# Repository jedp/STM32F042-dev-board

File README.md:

## STM32F042 Board

Dev board for the
[STM32F042](https://www.st.com/resource/en/datasheet/stm32f042c4.pdf).

Basic linker script, headers, hello world program, and notes are given in [programming](./programming).

Dimensions: 1.63in (41.50mm) x 0.74 in (18.80mm); headers 0.6in (15.24mm) center to center.

USB C receptacle for USB 2.0.

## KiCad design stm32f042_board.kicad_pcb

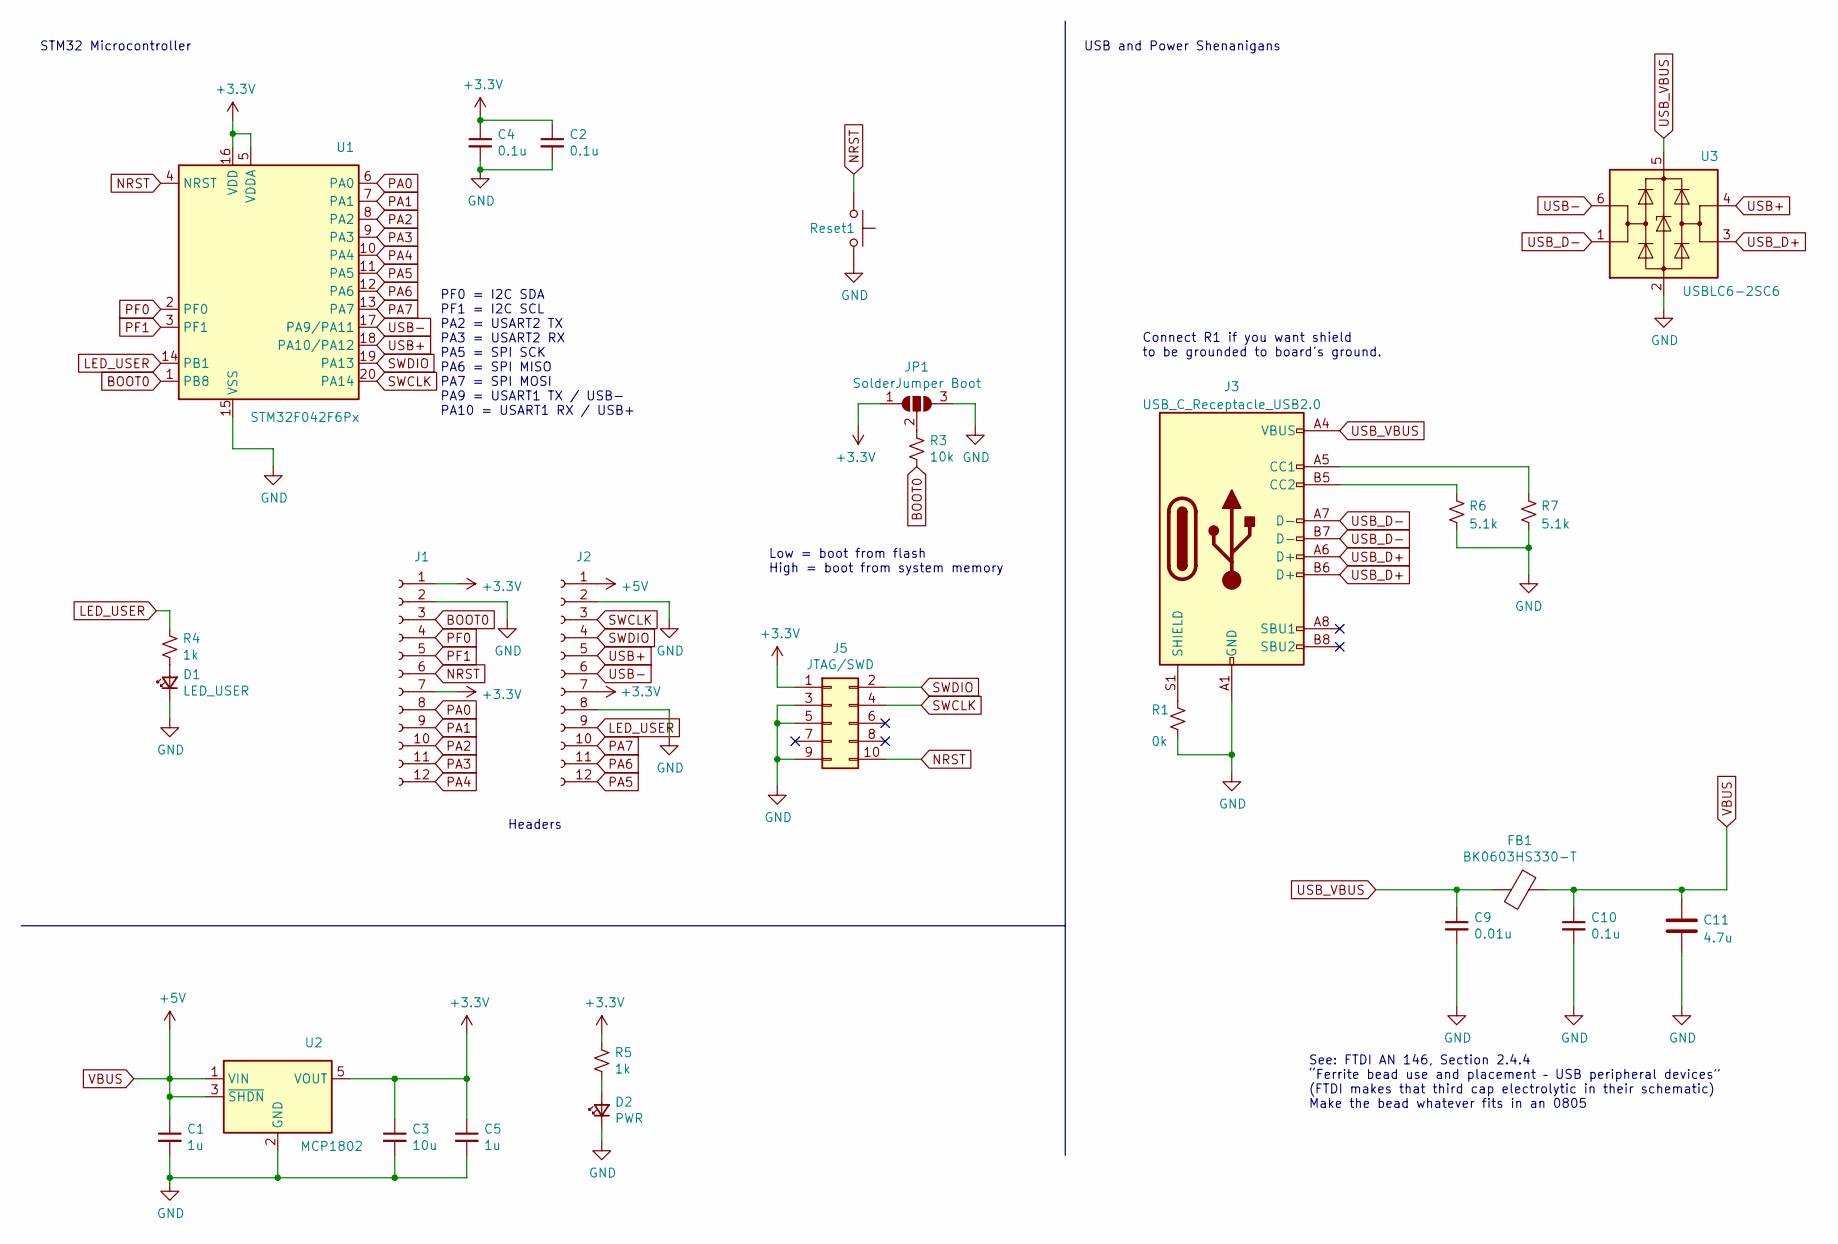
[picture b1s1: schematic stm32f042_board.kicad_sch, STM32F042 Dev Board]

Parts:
C1, C5: 1u; C_0805_2012Metric
C2, C4: 0.1u; C_0603_1608Metric
C3: 10u; C_0805_2012Metric
C9: 0.01u; C_0805_2012Metric
C10: 0.1u; C_0805_2012Metric
C11: 4.7u; C_1206_3216Metric
D1: LED_USER; LED_0603_1608Metric
D2: PWR; LED_0603_1608Metric
FB1: BK0603HS330-T; L_0805_2012Metric
J1, J2: Conn_01x12_Female; PinSocket_1x12_P2.54mm_Vertical
J3: USB_C_Receptacle_USB2.0; USB4105-GF-A
J5: JTAG/SWD; PinHeader_2x05_P1.27mm_Vertical
JP1: SolderJumper Boot; SolderJumper-3_P2.0mm_Open_TrianglePad1.0x1.5mm
R1: 0k; R_0603_1608Metric
R3: 10k; R_0603_1608Metric
R4, R5: 1k; R_0603_1608Metric
R6, R7: 5.1k; R_0603_1608Metric
Reset1: SW_Push; SW_SPST_B3U-1000P-B
U1: STM32F042F6Px; TSSOP-20_4.4x6.5mm_P0.65mm
U2: MCP1802; SOT-23-5
U3: USBLC6-2SC6; SOT-23-6

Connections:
+3V3: C2.1, C3.1, C4.1, C5.1, J1.1, J1.7, J2.7, J5.1, JP1.1 (A), R5.1, U1.5 (VDDA), U1.16 (VDD), U2.5 (VOUT)
BOOT0: J1.3, R3.2, U1.1 (PB8)
GND: C1.2, C2.2, C3.2, C4.2, C5.2, C9.2, C10.2, C11.2, D1.1 (K), D2.1 (K), J1.2, J2.2, J2.8, J3.A1 (GND), J3.A12 (GND), J3.B1 (GND), J3.B12 (GND), J5.3, J5.5, J5.9, JP1.3 (B), R1.2, R6.2, R7.2, Reset1.2, U1.15 (VSS), U2.2 (GND), U3.2 (GND)
LED_USER: J2.9, R4.1, U1.14 (PB1)
NRST: J1.6, J5.10, Reset1.1, U1.4 (NRST)
unnamed: D1.2 (A), R4.2
unnamed: D2.2 (A), R5.2
unnamed: J3.A5 (CC1), R7.1
unnamed: J3.B5 (CC2), R6.1
unnamed: J3.S1 (SHIELD), R1.1
unnamed: JP1.2 (C), R3.1
PA0: J1.8, U1.6 (PA0)
PA1: J1.9, U1.7 (PA1)
PA2: J1.10, U1.8 (PA2)
PA3: J1.11, U1.9 (PA3)
PA4: J1.12, U1.10 (PA4)
PA5: J2.12, U1.11 (PA5)
PA6: J2.11, U1.12 (PA6)
PA7: J2.10, U1.13 (PA7)
PF0: J1.4, U1.2 (PF0)
PF1: J1.5, U1.3 (PF1)
SWCLK: J2.3, J5.4, U1.20 (PA14)
SWDIO: J2.4, J5.2, U1.19 (PA13)
USB+: J2.5, U1.18 (PA10/PA12), U3.4 (I/O2)
USB-: J2.6, U1.17 (PA9/PA11), U3.6 (I/O1)
USB_D+: J3.A6 (D+), J3.B6 (D+), U3.3 (I/O2)
USB_D-: J3.A7 (D-), J3.B7 (D-), U3.1 (I/O1)
USB_VBUS: C9.1, FB1.2, J3.A4 (VBUS), J3.A9 (VBUS), J3.B4 (VBUS), J3.B9 (VBUS), U3.5 (VBUS)
VBUS: C1.1, C10.1, C11.1, FB1.1, J2.1, U2.1 (VIN), U2.3 (~SHDN)

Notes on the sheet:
Headers
Connect R1 if you want shield to be grounded to board's ground.
PF0 = I2C SDA PF1 = I2C SCL PA2 = USART2 TX PA3 = USART2 RX PA5 = SPI SCK PA6 = SPI MISO PA7 = SPI MOSI PA9 = USART1 TX / USB- PA10 = USART1 RX / USB+
STM32 Microcontroller
USB and Power Shenanigans
See: FTDI AN 146, Section 2.4.4 “Ferrite bead use and placement – USB peripheral devices” (FTDI makes that third cap electrolytic in their schematic) Make the bead whatever fits in an 0805
Low = boot from flash High = boot from system memory

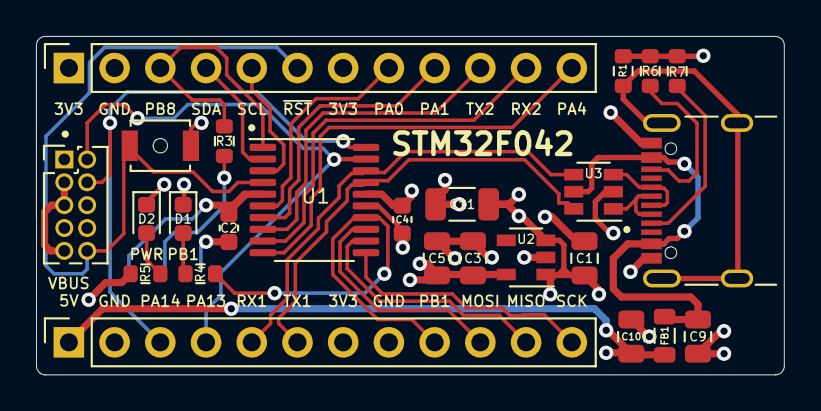
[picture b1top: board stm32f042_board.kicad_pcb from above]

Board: 4 copper layers, 41.6 x 18.8 mm, 26 parts (1 on the bottom side), 29 nets.

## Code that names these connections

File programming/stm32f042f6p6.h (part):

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 *
 * TSSOP20 Pinout, with alternate and additional functions.
 *
 *   1 PB8, BOOT0
 *   2 PF0, OSC_IN, CRS_SYNC, I2C1_SDA
 *   3 PF1, OSC_OUT, I2C1_SCL
 *   4 NRST
 *   5 VDDA
 *   6 PA0, USART2_CTS, TIM2_CH1_ETR, TSC_G1_IO1, RTC_TAMP2, WKUP1, ADC_IN0
 *   7 PA1, USART2_RTS, TIM2_CH2, TSC_G1_IO2, EVENTOUT, ADC_IN1
 *   8 PA2, USART2_TX, TIM2_CH3, TSC_G1_IO3, ADC_IN2, WKUP4
 *   9 PA3, USART2_RX, TIM2_CH4, TSC_G1_IO4, ADC_IN3
 *  10 PA4, SPI1_NSS, I2S1_WS, TIM14_CH1, TSC_G2_IO1, USART2_CK USB_NOE, ADC_IN4
 *  11 PA5, SPI1_SCK, I2S1_CK, CEC, TIM2_CH1_ETR, TSC_G2_IO2, ADC_IN5
 *  12 PA6, SPI1_MISO, I2S1_MCK, TIM3_CH1, TIM1_BKIN, TIM16_CH1, TSC_G2_IO3, EVENTOUT, ADC_IN6
 *  13 PA7, SPI1_MOSI, I2S1_SD, TIM3_CH2, TIM14_CH1, TIM1_CH1N, TIM17_CH1, TSC_G2_IO4, EVENTOUT, ADC_IN7
 *  14 PB1, TIM3_CH4, TIM14_CH1, TIM1_CH3N, TSC_G3_IO3, ADC_IN9
 *  15 VSS
 *  16 VDD
 *  17 PA9, USART1_TX, TIM1_CH2, TSC_G4_IO1, I2C1_SCL
 *     PA11, CAN_RX, USART1_CTS, TIM1_CH4, TSC_G4_IO3, EVENTOUT, I2C1_SCL, USB_DM
 *  18 PA10, USART1_RX, TIM1_CH3, TIM17_BKIN, TSC_G4_IO2, I2C1_SDA
 *     PA12, CAN_TX,USART1_RTS, TIM1_ETR, TSC_G4_IO4, EVENTOUT, I2C1_SDA, USB_DP
 *  19 PA13, IR_OUT, SWDIO USB_NOE
 *  20 PA14, USART2_TX, SWCLK
 */

#define BIT_0           (1 <<  0)
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
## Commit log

2021-02-10 jedboard v2
2021-03-03 move a via to reconnect the isolated 3V3 and GND pours (pins 1 and 2)
2021-03-18 oops. connect 3v3 on jtag header.
2021-03-18 make smaller
2021-03-19 update images for readme
2022-09-04 Hello World programming example.
2022-09-04 clean up makefile
2022-09-05 more programming documentation
2022-09-06 delay_ms
2022-09-06 fix typo
2023-03-07 Fix user LED ground; Update kicad version
2023-03-07 Add identifying text on rear silkscreen
2023-03-22 Bug fixes
2023-03-23 Migrate to KiCad 7
2023-04-09 Bug fixes
    - Un-migrate to v7 - oshpark not compatibile yet
    - Optionally ground USB shield to board via R 0k
    - Route Tx/Rx (USB D+/-) as diff pair to breakout pins
    - Fix missing +3V3 connection to JTAG pin 1
    - Four-layer board
    - Remove unnecessary gaps in copper now that board is four layers
2023-04-09 Revert "Migrate to KiCad 7"
    This reverts commit a80925b01a00ac2b6e233b577ff1a59522959ffa.
    - Footprints and some other things don't seem to work right yet
    - OSHPark not v7 compatible yet.
2023-04-09 Replace USB Micro receptacle with USB C
2023-04-09 Add BOM and component groups to readme
2023-04-27 Finished board photo (USB-C)
2023-04-27 Link to Micro-USB tag from readme
